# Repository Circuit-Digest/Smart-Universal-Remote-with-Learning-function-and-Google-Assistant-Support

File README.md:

# [Smart-Universal-Remote-with-Learning-function-and-Google-Assistant-Support](https://circuitdigest.com/microcontroller-projects/diy-smart-universal-ir-remote-controle)

<br>

<br>

<br>

[<h1>Click here](https://circuitdigest.com/tags/ESP32) For other ESP32 tutorials.</h1>

<br>
<br>
In our day-to-day life, we use various gadgets such as television, set-top boxes, air conditioners, home theatre, DVD players, and many other remote-operated devices. Different gadgets means maintaining different remote controls which are not only clumsy but also difficult to manage. Universal remote control simplifies our life because it helps us control any IR devices in our daily life. So in this project we are going to build a single IR-based universal remote which can control all available IR-remote controlled electronic gadgets. 

<br>
[Note: As this projects are very simple we are only providing the code, schemaitic, and a few essential images if you want to get the images or code explanations do check out the Circuit Digest website.
<br>
<br>

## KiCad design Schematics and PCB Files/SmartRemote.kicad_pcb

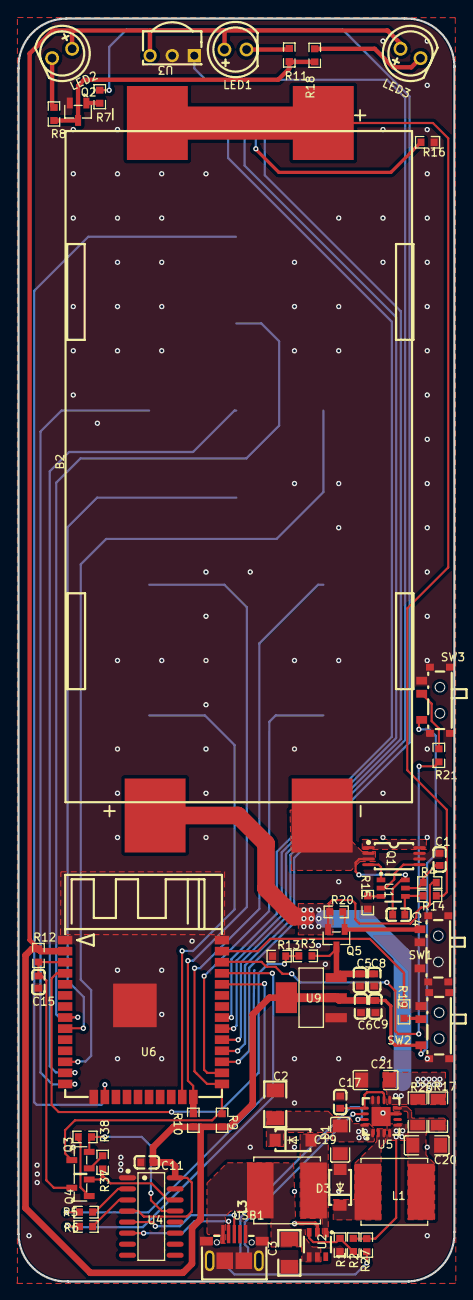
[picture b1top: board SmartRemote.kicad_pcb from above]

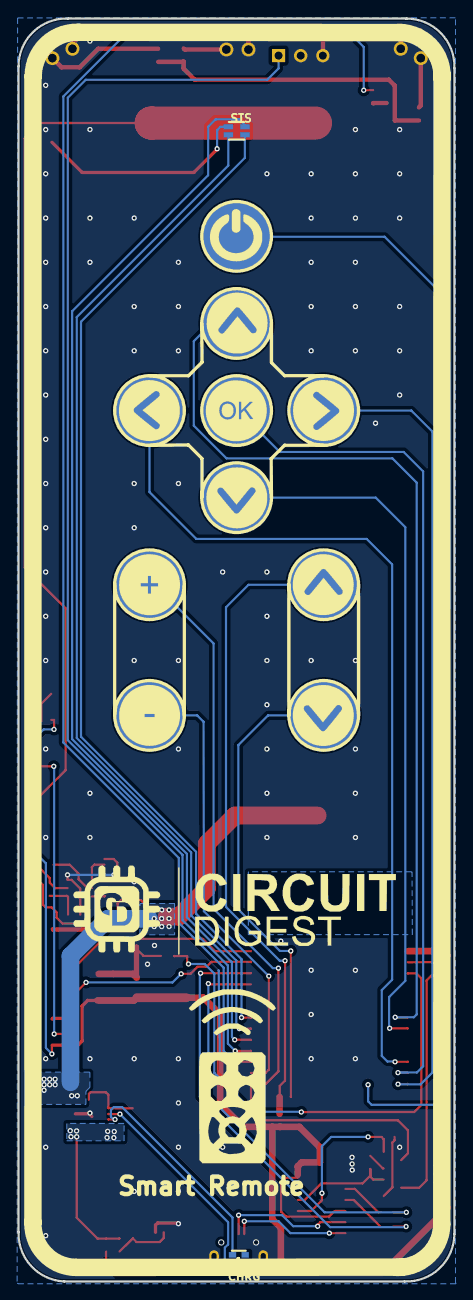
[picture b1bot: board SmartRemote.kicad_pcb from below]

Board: 2 copper layers, 50.0 x 145.0 mm, 75 parts (11 on the bottom side), 60 nets.

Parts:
B2: Li-ion 18650 SMD 1s2p; LI-ION 18650 DUAL SMD
C1, C4, C17: 0.1u; C0603
C2, C3: 22uF; 1206
C5, C6: 10u; C0603
C8, C9, C11: 100nF; C0603
C15: 1n; C0603
C19, C20, C21: 10UF; C1206
CHRG: TZ-P4-1615RGBTCA1-0.55T; LED-SMD_4P-L1.6-W1.5-BR_TZ-P4-1615
D1, D3: SS34; SMA(DO-214AC)
L1, L3: 22uH; IND-SMD_L7.0-W6.8
LED1, LED2, LED3: MHL5013UBDWT; LED-TH_BD5.0-P2.54-L-RD_WHITE
Q1: 8205A; TSSOP-8_L4.4-W3.0-P0.65-LS6.4-BL
Q2, Q3, Q4: S8050; SOT-23-3_L2.9-W1.3-P1.90-LS2.4-BR
Q5: AO3401; SOT-23-3_L2.9-W1.3-P1.90-LS2.4-BR
R1: 1.2KΩ; R0603_NEW
R2: 22k; R0603
R3: 100k; R0603
R4, R14: 330; R0603
R5, R6: 470; R0603_NEW
R7: 680; R0603
R8, R11, R16, R18: 1k; R0603
R9, R10: 4.7K; R0603_NEW
R12, R19, R21: 10k; R0603_NEW
R13: 47k; R0603
R15: 2k; R0603
R17, R26: 100R; R1206
R20, R37, R38: 10K; R0603_NEW
R27: 1k; R0603_NEW
STS: TJ-S1615CY6TGLCCSRGB-A5; LED-ARRAY-SMD_4P-L1.6-W1.5-BL-FD
SW1, SW2, SW3: K3-1296S-E2; SW-SMD_K3-1296S-E2
T1, T2, T3, T4, T5, T6, T7, T8, T9, T10: Touchpad; TOUCH_D1
U1: HY2120CB; SOT-23-6_L2.9-W1.6-P0.95-LS2.8-BR
U2: MT3608; SOT-23-6_L2.9-W1.6-P0.95-LS2.8-BR
U3: VS1838B; OPTO-TH_VS1838B
U4: CH340G; SOIC-16_L9.9-W3.9-P1.27-LS6.0-BL
U5: TP5100; QFN-16_L4.0-W4.0-P0.65-BL-EP2.2
U6: ESP32-WROOM-32; WIFIM-SMD_ESP-32S
U9: AMS1117-3.3; SOT-223_L6.5-W3.5-P2.30-LS7.0-BR
USB1: MICRO5.9MMUSB; MICRO-USB-SMD_5P-P0.65-H-F_MICRO5.9MMUSB

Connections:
+3.3V: C6.1, C9.2, C11.2, LED1.2, LED2.2, LED3.2, R9.2, R10.2, R12.2, SW2.1, SW3.1, U3.3, U4.4, U4.16, U6.2, U9.2, U9.4
B-: B2.4, C4.1, Q1.2, Q1.3, U1.6
BATV_SENSE: R3.1, R13.2, U6.4
C17_2: C17.2, U5.10, U5.13
D+: U4.5, USB1.3
D-: U4.6, USB1.2
EN: C15.2, Q4.3, R12.1, U6.3
GND: C1.2, C2.1, C3.1, C5.2, C6.2, C8.1, C9.1, C11.1, C15.1, C17.1, C19.2, C20.2, C21.2, D3.1, Q1.6, Q1.7, Q2.2, R1.1, R13.1, R15.1, R16.1, SW1.1, SW1.2, SW1.4, SW1.5, SW1.6, SW1.7, SW2.3, SW2.4, SW2.5, SW2.6, SW2.7, SW3.3, SW3.4, SW3.5, SW3.6, SW3.7, U2.2, U3.2, U4.1, U5.7, U5.11, U5.12, U5.17, U6.1, U6.15, U6.38, U6.39, U9.1, USB1.5, USB1.6
IR_RX: U3.1, U6.28
IR_TX: R7.1, U6.27
L1_1: C20.1, L1.1, R17.2, R26.2, U5.8
L1_2: D3.2, L1.2, U5.2, U5.3
L3_1: C3.2, L3.1, U2.4, U2.5, USB1.1
L3_2: D1.1, L3.2, U2.1
LEARNSWITCH: R21.2, U6.36
LED1_1: LED1.1, R11.2
LED2_1: LED2.1, R8.2
LED3_1: LED3.1, R18.2
LED4_1: CHRG.1, U5.14
LED4_2: CHRG.2, U5.15
MODESWITCH: R19.2, U6.37
Q1_1: Q1.1, Q1.8
Q2_1: Q2.1, R7.2
Q2_3: Q2.3, R8.1, R11.1, R18.1
Q3_1: Q3.1, R37.2
Q3_2: Q3.2, R38.1, U4.13
Q4_1: Q4.1, R38.2
Q4_2: Q4.2, R37.1, U4.14
R1_2: R1.2, R2.1, U2.3
R4_2: C1.1, R4.2, U1.5
R5_2: R5.2, U4.2
R6_2: R6.2, U4.3
R14_1: B2.2, B2.3, R14.1
R14_2: C4.2, R14.2, U1.4
R15_2: R15.2, U1.3
R16_2: R16.2, STS.4
R19_1: R19.1, SW2.2
R27_1: CHRG.4, R27.1
RXD0: R5.1, U6.34
SW1_3: Q5.1, R20.1, SW1.3
SW3_2: R21.1, SW3.2
TOUCH0: T1.1, U6.26
TOUCH1: Q3.3, R9.1, T2.1, U6.25
TOUCH2: R10.1, T3.1, U6.24
TOUCH3: T4.1, U6.23
TOUCH4: T5.1, U6.16
TOUCH5: T6.1, U6.14
TOUCH6: T7.1, U6.13
TOUCH7: T8.1, U6.12
TOUCH8: T9.1, U6.9
TOUCH9: T10.1, U6.8
TXD0: R6.1, U6.35
U1_1: Q1.4, U1.1
U1_2: Q1.5, U1.2
U6_29: STS.3, U6.29
U6_30: STS.1, U6.30
U6_31: STS.2, U6.31
VBAT: B2.1, C21.1, Q5.2, R4.1, R17.1, R20.2, R26.1, U5.9
VBATSW: C5.1, C8.2, Q5.3, R3.2, U9.3
VBOOST: C2.2, C19.1, D1.2, R2.2, R27.2, U5.1, U5.4, U5.5, U5.16

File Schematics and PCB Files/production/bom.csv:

Designator,Footprint,Quantity,Value,LCSC Part #
B2,LI-ION 18650 DUAL SMD,1,Li-ion 18650 SMD 1s2p,
"C1, C17, C4",C0603,3,0.1u,
"C11, C8, C9",C0603,3,100nF,
C15,C0603,1,1n,
"C19, C20, C21",C1206,3,10UF,
"C2, C3",1206,2,22uF,
"C5, C6",C0603,2,10u,
CHRG,LED-SMD_4P-L1.6-W1.5-BR_TZ-P4-1615,1,TZ-P4-1615RGBTCA1-0.55T,
"D1, D3",SMA(DO-214AC),2,SS34,
"L1, L3",IND-SMD_L7.0-W6.8,2,22uH,
"LED1, LED2, LED3",LED-TH_BD5.0-P2.54-L-RD_WHITE,3,MHL5013UBDWT,
Q1,TSSOP-8_L4.4-W3.0-P0.65-LS6.4-BL,1,8205A,
"Q2, Q3, Q4",SOT-23-3_L2.9-W1.3-P1.90-LS2.4-BR,3,S8050,
Q5,SOT-23-3_L2.9-W1.3-P1.90-LS2.4-BR,1,AO3401,
R1,R0603_NEW,1,1.2KΩ,
"R10, R9",R0603_NEW,2,4.7K,
"R11, R16, R18, R8",R0603,4,1k,
"R12, R19, R20, R21, R37, R38",R0603_NEW,6,10k,
R13,R0603,1,47k,
"R14, R4",R0603,2,330,
R15,R0603,1,2k,
"R17, R26",R1206,2,100R,
R2,R0603,1,22k,
R27,R0603_NEW,1,1k,
R3,R0603,1,100k,
"R5, R6",R0603_NEW,2,470,
R7,R0603,1,680,
STS,LED-ARRAY-SMD_4P-L1.6-W1.5-BL-FD,1,TJ-S1615CY6TGLCCSRGB-A5,
"SW1, SW2, SW3",SW-SMD_K3-1296S-E2,3,K3-1296S-E2,
"T1, T10, T2, T3, T4, T5, T6, T7, T8, T9",TOUCH_D1,10,Touchpad,
U1,SOT-23-6_L2.9-W1.6-P0.95-LS2.8-BR,1,HY2120CB,
U2,SOT-23-6_L2.9-W1.6-P0.95-LS2.8-BR,1,MT3608,
U3,OPTO-TH_VS1838B,1,VS1838B,
U4,SOIC-16_L9.9-W3.9-P1.27-LS6.0-BL,1,CH340G,
U5,QFN-16_L4.0-W4.0-P0.65-BL-EP2.2,1,TP5100,
U6,WIFIM-SMD_ESP-32S,1,ESP32-WROOM-32,
U9,SOT-223_L6.5-W3.5-P2.30-LS7.0-BR,1,AMS1117-3.3,
USB1,MICRO-USB-SMD_5P-P0.65-H-F_MICRO5.9MMUSB,1,MICRO5.9MMUSB,
